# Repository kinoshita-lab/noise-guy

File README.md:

# noise-guy kit

[Document in Japanese](README_ja.md)

Tiny white noise generator made by ATTiny10

# Kit contents

- Pre-assembled/programmed circuit board
- 1x3 pin vertical header

# How to assemble

Solder the 1x3 pin.

# How to use

- Connect power source. This product use ATTiny10 with 8MHz configuration. Vcc must be within the range between 2.7V - 5.5V(cf. ATtiny10 datasheet)
- Add DC Cut capacitor to "Out" terminal externally, to meet your specification(typically 100uF - 470uF).

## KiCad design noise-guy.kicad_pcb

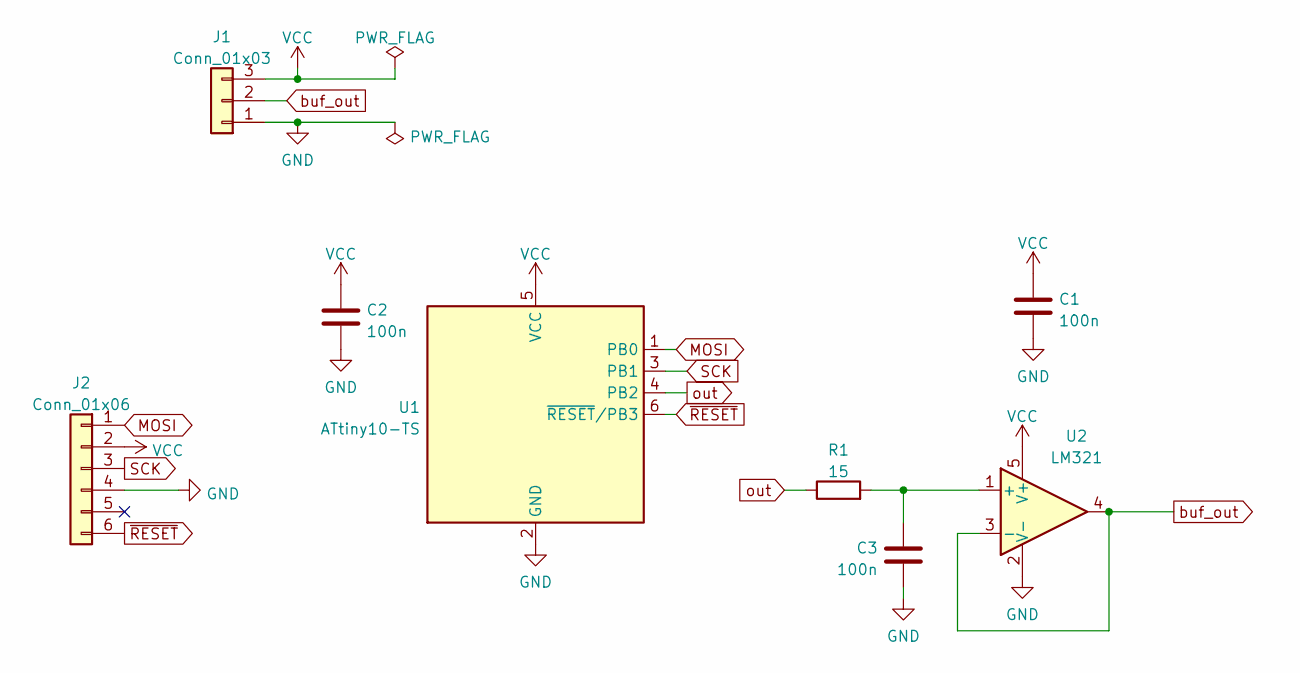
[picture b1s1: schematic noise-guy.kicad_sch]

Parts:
C1, C2, C3: 100n; C_0402_1005Metric; LCSC C1525
J1: Conn_01x03; PinHeader_1x03_P2.54mm_Vertical
J2: Conn_01x06; conn_01x06_attiny_JIG
R1: 15; R_0402_1005Metric; LCSC C25083
U1: ATtiny10-TS; SOT-23-6; LCSC C128438
U2: LM321; SOT-23-5; LCSC C686637

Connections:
GND: C1.2, C2.2, C3.2, J1.1, J2.4, U1.2 (GND), U2.2 (V-)
MOSI: J2.1, U1.1 (PB0)
unnamed: C3.1, R1.2, U2.1 (+)
SCK: J2.3, U1.3 (PB1)
VCC: C1.1, C2.1, J1.3, J2.2, U1.5 (VCC), U2.5 (V+)
buf_out: J1.2, U2.3 (-), U2.4
out: R1.1, U1.4 (PB2)
~RESET: J2.6, U1.6 (~RESET/PB3)

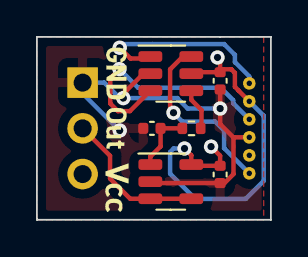
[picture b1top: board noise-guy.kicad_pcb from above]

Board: 2 copper layers, 13.0 x 10.2 mm, 8 parts (0 on the bottom side), 8 nets.

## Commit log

2022-11-19 add schematics,soft
2022-11-19 add pdf for schematics, pcb w/ dimension
2022-11-20 add readme
2022-11-20 Create LICENSE
